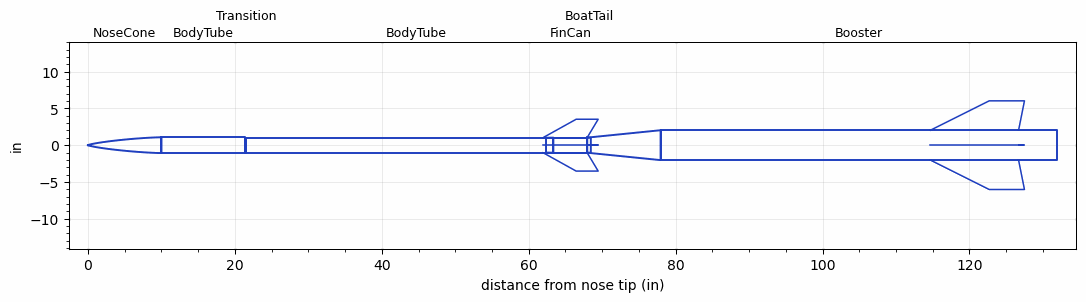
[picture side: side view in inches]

<RASAeroDocument>
 <FileVersion>2</FileVersion>
 <RocketDesign>
  <NoseCone>
   <Length>10</Length>
   <Diameter>2.15</Diameter>
   <Shape>Von Karman Ogive</Shape>
   <BluntRadius>0.04</BluntRadius>
   <Location>0</Location>
  </NoseCone>
  <BodyTube>
   <Length>11.417</Length>
   <Diameter>2.15</Diameter>
   <Location>10</Location>
  </BodyTube>
  <Transition>
   <Length>0.12</Length>
   <Diameter>2.008</Diameter>
   <Location>21.417</Location>
   <RearDiameter>2.008</RearDiameter>
  </Transition>
  <BodyTube>
   <Length>46.42</Length>
   <Diameter>2.008</Diameter>
   <Location>21.537</Location>
  </BodyTube>
  <FinCan>
   <Length>4.6</Length>
   <Diameter>2.055</Diameter>
   <InsideDiameter>2.008</InsideDiameter>
   <Location>67.957</Location>
   <ShoulderLength>1</ShoulderLength>
   <Offset>-4.6</Offset>
   <Fin>
    <Count>4</Count>
    <Chord>6</Chord>
    <Span>2.5</Span>
    <SweepDistance>4.5</SweepDistance>
    <TipChord>3</TipChord>
    <Thickness>0.1</Thickness>
    <Location>6</Location>
    <AirfoilSection>Hexagonal</AirfoilSection>
    <FX1>1.6</FX1>
    <FX3>1.6</FX3>
   </Fin>
  </FinCan>
  <BoatTail>
   <Length>0.5</Length>
   <Diameter>2.055</Diameter>
   <RearDiameter>2.054</RearDiameter>
   <Location>67.957</Location>
  </BoatTail>
  <Booster>
   <Length>53.94</Length>
   <Diameter>4.07</Diameter>
   <InsideDiameter>2.055</InsideDiameter>
   <Location>67.957</Location>
   <ShoulderLength>10</ShoulderLength>
   <Fin>
    <Count>4</Count>
    <Chord>12</Chord>
    <Span>4</Span>
    <SweepDistance>8</SweepDistance>
    <TipChord>4.8</TipChord>
    <Thickness>0.35</Thickness>
    <Location>17.2</Location>
    <AirfoilSection>Hexagonal</AirfoilSection>
    <FX1>1.7</FX1>
    <FX3>1.7</FX3>
   </Fin>
  </Booster>
  <Surface>Camouflage Paint</Surface>
  <ModifiedBarrowman>True</ModifiedBarrowman>
  <Turbulence>True</Turbulence>
  <UseBooster1>False</UseBooster1>
  <UseBooster2>False</UseBooster2>
 </RocketDesign>
 <LaunchSite>
  <Altitude>3907</Altitude>
  <Pressure>0</Pressure>
  <RodAngle>2</RodAngle>
  <RodLength>8</RodLength>
  <Temperature>65</Temperature>
  <WindSpeed>20</WindSpeed>
 </LaunchSite>
 <Recovery>
  <Altitude1>1000</Altitude1>
  <Altitude2>1000</Altitude2>
  <DeviceType1>Parachute</DeviceType1>
  <DeviceType2>Parachute</DeviceType2>
  <Event1>True</Event1>
  <Event2>True</Event2>
  <Size1>8</Size1>
  <Size2>36</Size2>
  <EventType1>Apogee</EventType1>
  <EventType2>Altitude</EventType2>
  <CD1>1.33</CD1>
  <CD2>1.33</CD2>
 </Recovery>
 <SimulationList>
  <Simulation>
   <SustainerEngine>M1378LRCFRP  (Loki)</SustainerEngine>
   <SustainerLaunchWt>9.89</SustainerLaunchWt>
   <SustainerNozzleDiameter>2.04</SustainerNozzleDiameter>
   <SustainerCG>41</SustainerCG>
   <SustainerIgnitionDelay>15</SustainerIgnitionDelay>
   <Booster1Engine>N5500  (Loki)</Booster1Engine>
   <Booster1LaunchWt>45.92</Booster1LaunchWt>
   <Booster1SeparationDelay>0</Booster1SeparationDelay>
   <Booster1IgnitionDelay>0</Booster1IgnitionDelay>
   <Booster1CG>87.91</Booster1CG>
   <Booster1NozzleDiameter>3.87</Booster1NozzleDiameter>
   <IncludeBooster1>True</IncludeBooster1>
   <Booster2Delay>0</Booster2Delay>
   <IncludeBooster2>False</IncludeBooster2>
   <TimetoApogee>246.7657</TimetoApogee>
   <MaxAltitude>868217.8</MaxAltitude>
   <MaxVelocity>7778.802</MaxVelocity>
   <OptimumWt>7.136146</OptimumWt>
   <OptimumMaxAlt>7.136146</OptimumMaxAlt>
  </Simulation>
  <Simulation>
   <SustainerEngine>M1378LRCFRP  (Loki)</SustainerEngine>
   <SustainerLaunchWt>10.39</SustainerLaunchWt>
   <SustainerNozzleDiameter>1.95</SustainerNozzleDiameter>
   <SustainerCG>41</SustainerCG>
   <SustainerIgnitionDelay>14</SustainerIgnitionDelay>
   <Booster1Engine>N5500  (Loki)</Booster1Engine>
   <Booster1LaunchWt>47.42</Booster1LaunchWt>
   <Booster1SeparationDelay>1</Booster1SeparationDelay>
   <Booster1IgnitionDelay>0</Booster1IgnitionDelay>
   <Booster1CG>87.94</Booster1CG>
   <Booster1NozzleDiameter>3.878</Booster1NozzleDiameter>
   <IncludeBooster1>True</IncludeBooster1>
   <Booster2Delay>0</Booster2Delay>
   <IncludeBooster2>False</IncludeBooster2>
   <TimetoApogee>219.2914</TimetoApogee>
   <MaxAltitude>678422.9</MaxAltitude>
   <MaxVelocity>6984.634</MaxVelocity>
  </Simulation>
 </SimulationList>
</RASAeroDocument>
